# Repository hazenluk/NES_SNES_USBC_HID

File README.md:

# NES_SNES_USBC_HID
ATmega32u4-based NES + SNES controller to USB-C adapter. KiCad Project.

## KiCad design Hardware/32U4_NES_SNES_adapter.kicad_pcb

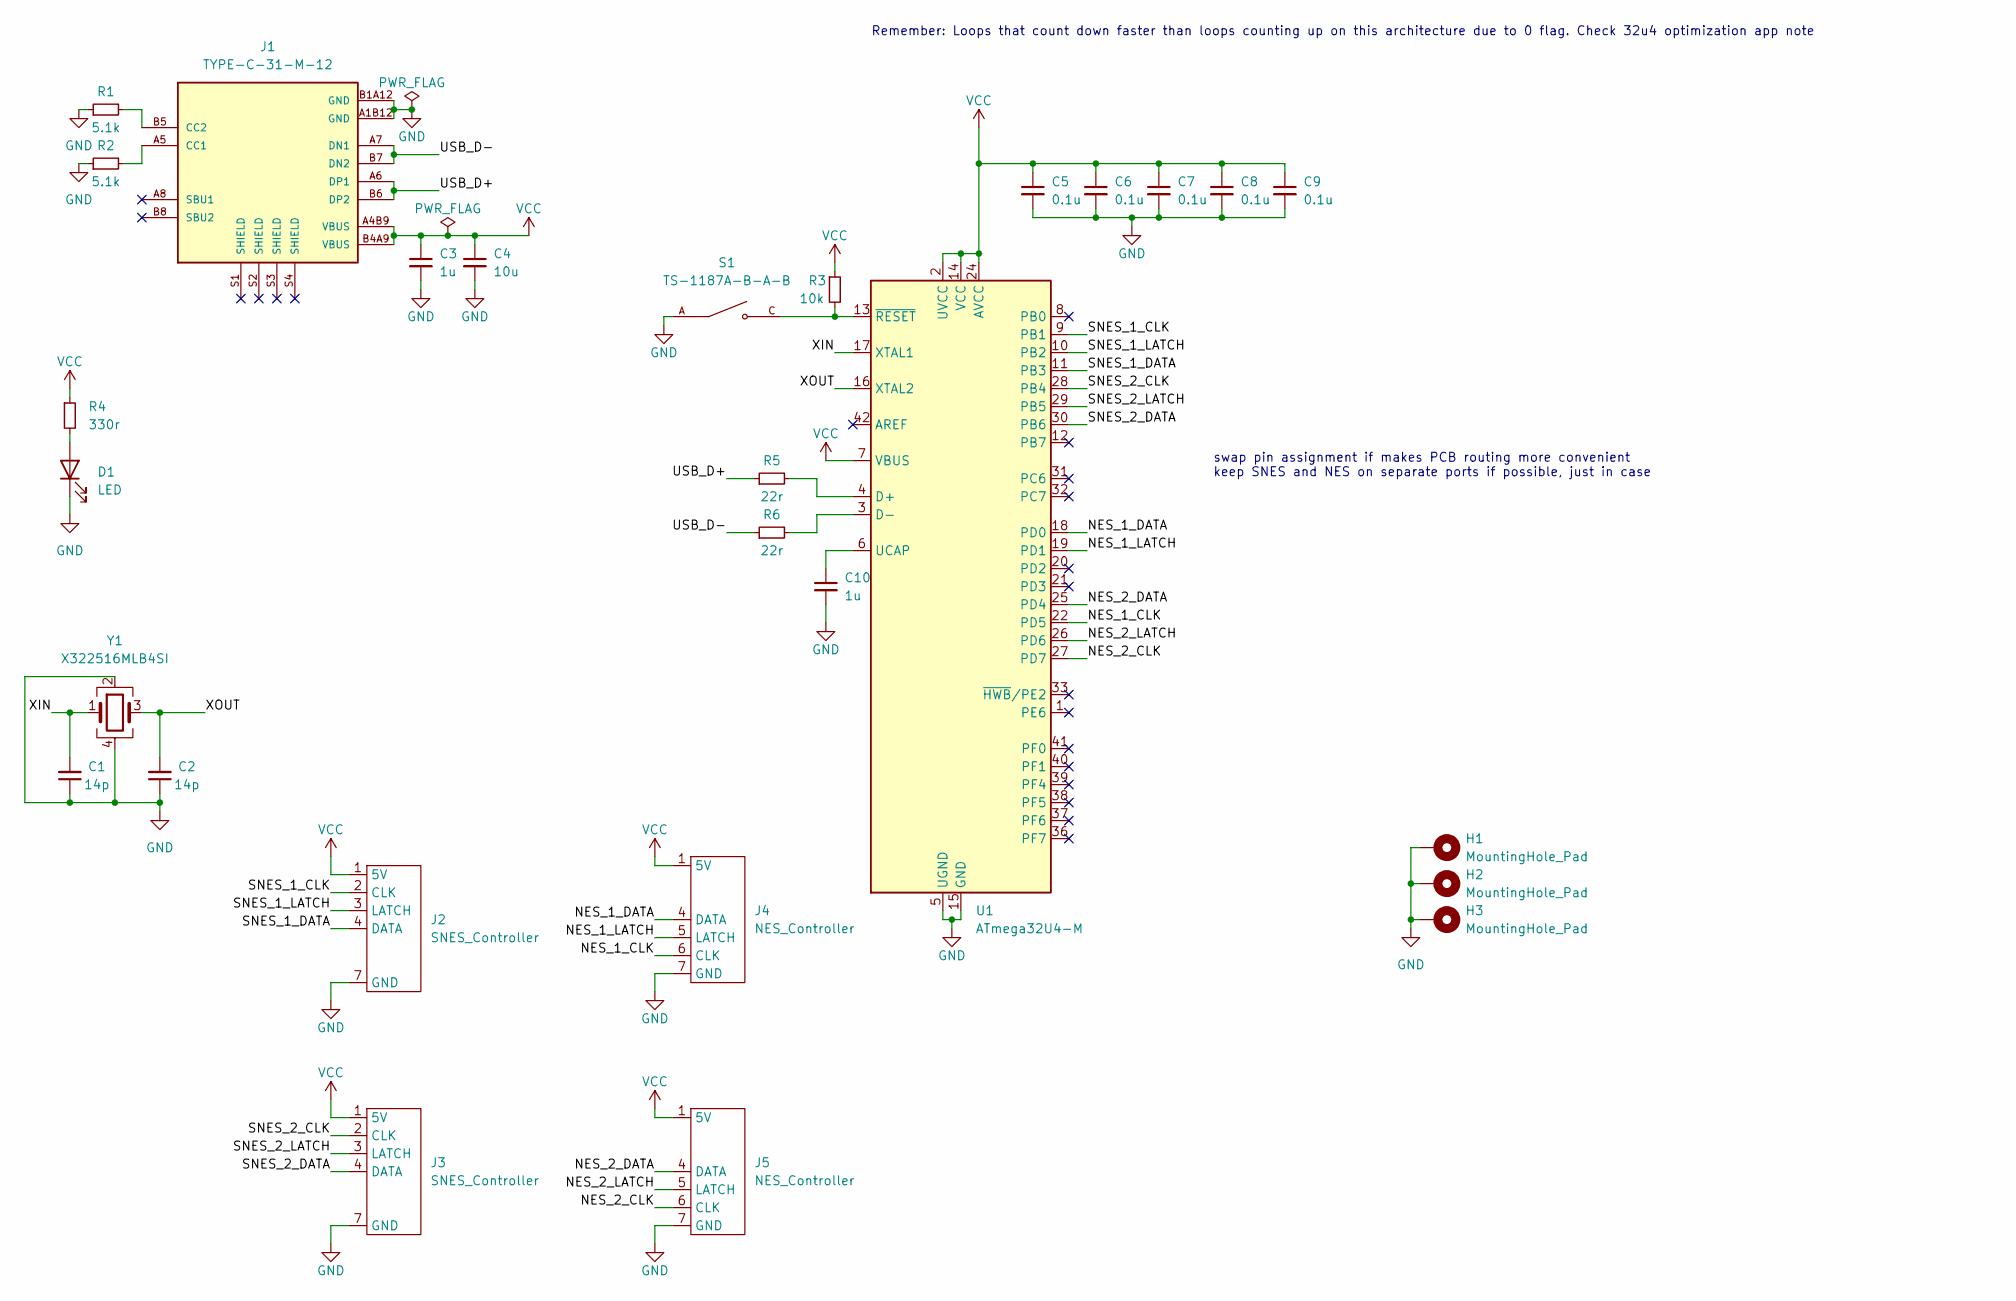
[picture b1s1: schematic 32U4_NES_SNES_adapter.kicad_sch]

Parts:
C1, C2: 14p; C_0402_1005Metric
C3, C10: 1u; C_0402_1005Metric
C4: 10u; C_0805_2012Metric
C5, C6, C7, C8, C9: 0.1u; C_0402_1005Metric
D1: LED; LED_0603_1608Metric
H1, H2, H3: MountingHole_Pad; MountingHole_3.2mm_M3_DIN965_Pad
J1: TYPE-C-31-M-12; HRO_TYPE-C-31-M-12; PARTREV A
J2, J3: SNES_Controller; GAMING_SNES
J4, J5: NES_Controller; NES controller port
R1, R2: 5.1k; R_0402_1005Metric
R3: 10k; R_0402_1005Metric
R4: 330r; R_0402_1005Metric
R5, R6: 22r; R_0402_1005Metric
S1: TS-1187A-B-A-B; SW_TS-1187A-B-A-B; PARTREV A0
U1: ATmega32U4-M; QFN-44-1EP_7x7mm_P0.5mm_EP5.2x5.2mm
Y1: X322516MLB4SI; Crystal_SMD_3225-4Pin_3.2x2.5mm

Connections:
/NES_1_CLK: J4.6 (CLK), U1.22 (PD5)
/NES_1_DATA: J4.4 (DATA), U1.18 (PD0)
/NES_1_LATCH: J4.5 (LATCH), U1.19 (PD1)
/NES_2_CLK: J5.6 (CLK), U1.27 (PD7)
/NES_2_DATA: J5.4 (DATA), U1.25 (PD4)
/NES_2_LATCH: J5.5 (LATCH), U1.26 (PD6)
/SNES_1_CLK: J2.2 (CLK), U1.9 (PB1)
/SNES_1_DATA: J2.4 (DATA), U1.11 (PB3)
/SNES_1_LATCH: J2.3 (LATCH), U1.10 (PB2)
/SNES_2_CLK: J3.2 (CLK), U1.28 (PB4)
/SNES_2_DATA: J3.4 (DATA), U1.30 (PB6)
/SNES_2_LATCH: J3.3 (LATCH), U1.29 (PB5)
/USB_D+: J1.A6 (DP1), J1.B6 (DP2), R5.1
/USB_D-: J1.A7 (DN1), J1.B7 (DN2), R6.1
/XIN: C1.2, U1.17 (XTAL1), Y1.1
/XOUT: C2.2, U1.16 (XTAL2), Y1.3
GND: C1.1, C2.1, C3.2, C4.2, C5.2, C6.2, C7.2, C8.2, C9.2, C10.2, D1.1 (K), H1.1, H2.1, H3.1, J1.A1B12 (GND), J1.B1A12 (GND), J2.7 (GND), J3.7 (GND), J4.7 (GND), J5.7 (GND), R1.1, R2.1, S1.A, S1.B, U1.5 (UGND), U1.15 (GND), U1.23 (GND), U1.35 (GND), U1.43 (GND), U1.45 (GND), Y1.2, Y1.4
unnamed: C10.1, U1.6 (UCAP)
unnamed: D1.2 (A), R4.2
unnamed: J1.A5 (CC1), R2.2
unnamed: J1.B5 (CC2), R1.2
unnamed: R3.2, S1.C, S1.D, U1.13 (~RESET)
unnamed: R5.2, U1.4 (D+)
unnamed: R6.2, U1.3 (D-)
VCC: C3.1, C4.1, C5.1, C6.1, C7.1, C8.1, C9.1, J1.A4B9 (VBUS), J1.B4A9 (VBUS), J2.1 (5V), J3.1 (5V), J4.1 (5V), J5.1 (5V), R3.1, R4.1, U1.2 (UVCC), U1.7 (VBUS), U1.14 (VCC), U1.24 (AVCC), U1.34 (VCC), U1.44 (AVCC)

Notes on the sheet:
Remember: Loops that count down faster than loops counting up on this architecture due to 0 flag. Check 32u4 optimization app note
swap pin assignment if makes PCB routing more convenient keep SNES and NES on separate ports if possible, just in case

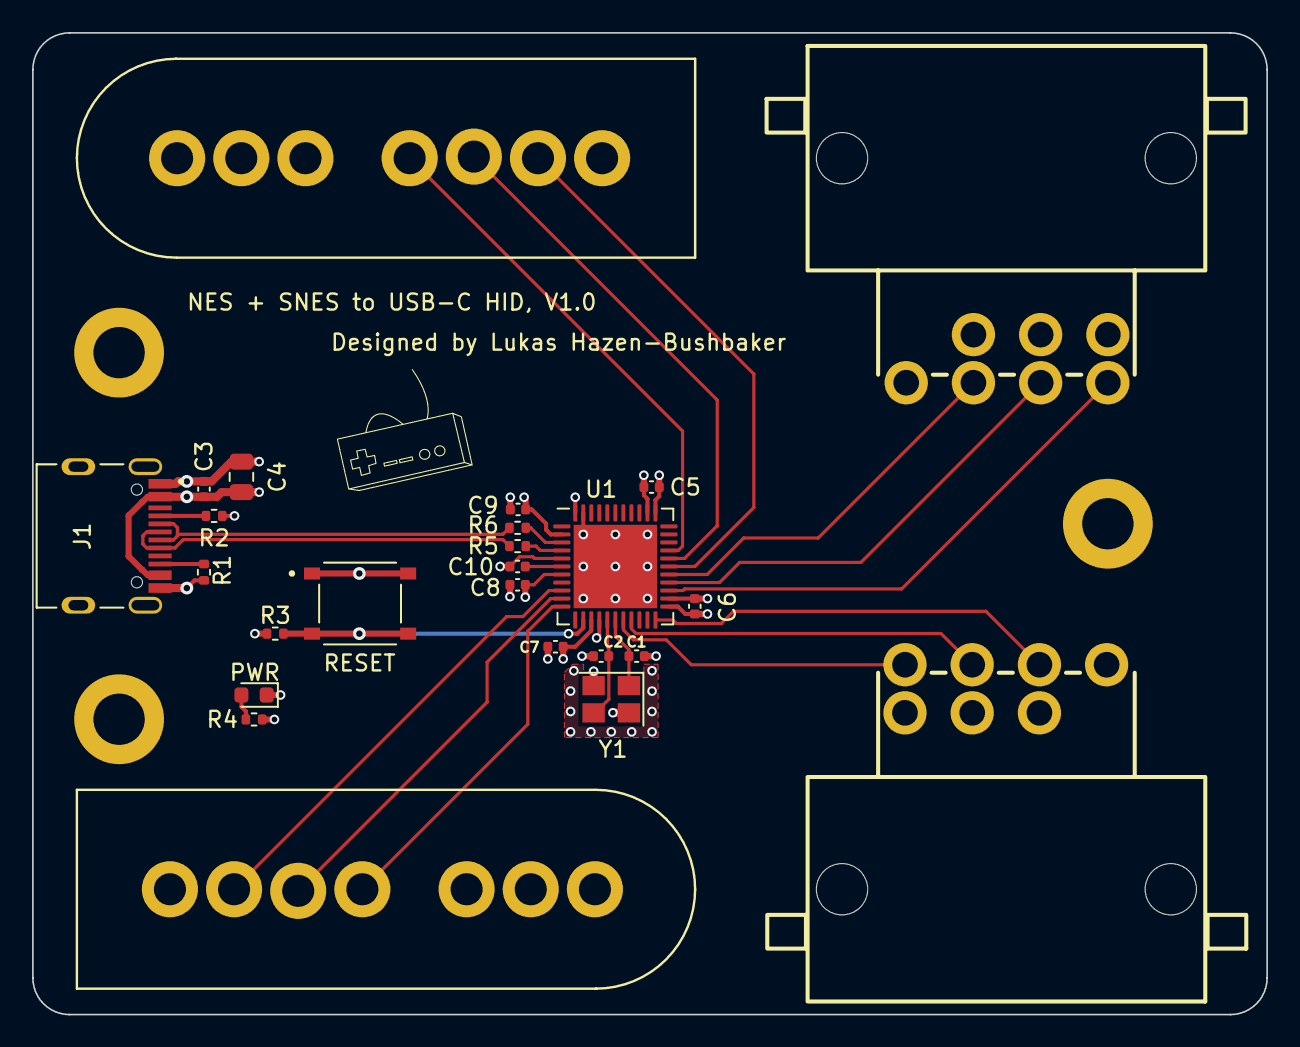
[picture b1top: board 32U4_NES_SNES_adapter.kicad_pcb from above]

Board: 4 copper layers, 77.0 x 61.2 mm, 28 parts (0 on the bottom side), 25 nets.

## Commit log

2023-09-14 Init commit
2023-09-20 Re-organized file structure
